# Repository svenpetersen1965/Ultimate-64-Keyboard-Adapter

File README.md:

# Ultimate-64-Keyboard-Adapter
This is an extension for the Ultimate 64 (elite) keyboard connector to get it into a position, that can be reached easily with the standard length keyboard cable. 

The project includes a 3D printed 16mm stand off, that fits the mounting hole. It fits with this 3D printed <a href="https://www.thingiverse.com/thing:3220123">mounting bracket</a> that can be found on thingiverse.com.

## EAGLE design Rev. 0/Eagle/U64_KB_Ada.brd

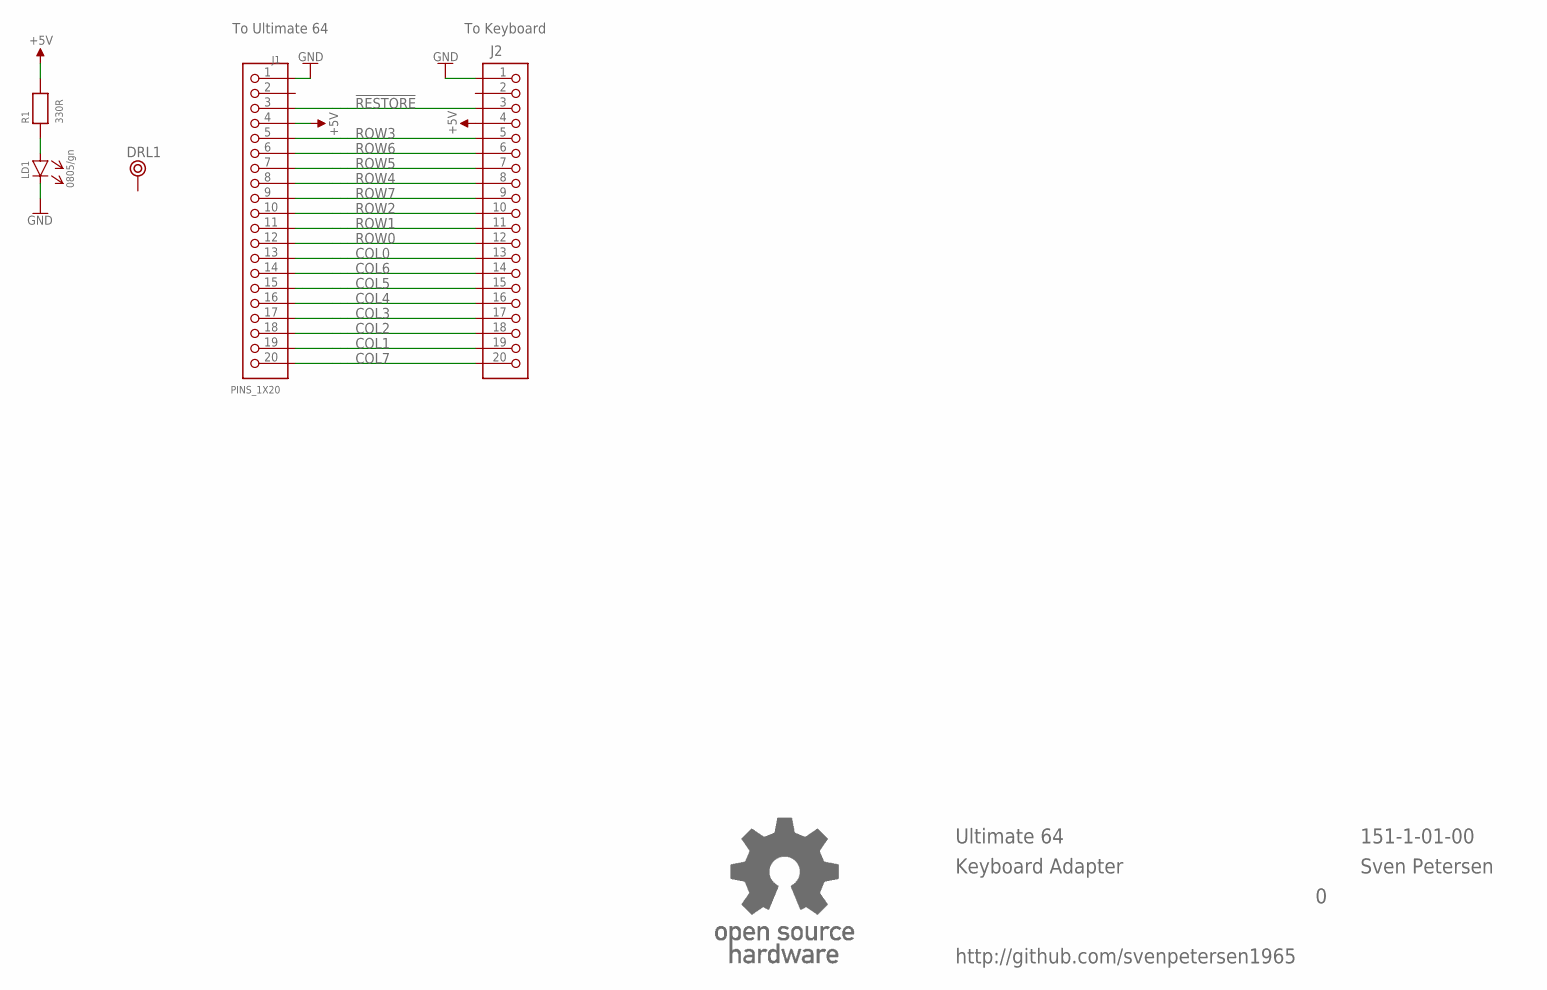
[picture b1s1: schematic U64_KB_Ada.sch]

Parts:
DRL1: BOHR3,5
J1: PINS_1X20; PINS_1X20V
J2: PINHD-1X20; 1X20
LD1: 0805/gn; 0805
R1: 330R; 0805
U$12: OPEN_SOURCE_HW; OPENHW

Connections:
!RESTORE: J1.3, J2.3
+5V: J1.4, J2.4, R1.2
COL0: J1.13, J2.13
COL1: J1.19, J2.19
COL2: J1.18, J2.18
COL3: J1.17, J2.17
COL4: J1.16, J2.16
COL5: J1.15, J2.15
COL6: J1.14, J2.14
COL7: J1.20, J2.20
GND: J1.1, J2.1, LD1.K
unnamed: LD1.A, R1.1
ROW0: J1.12, J2.12
ROW1: J1.11, J2.11
ROW2: J1.10, J2.10
ROW3: J1.5, J2.5
ROW4: J1.8, J2.8
ROW5: J1.7, J2.7
ROW6: J1.6, J2.6
ROW7: J1.9, J2.9

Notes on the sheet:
To Keyboard
To Ultimate 64
Ultimate 64
Keyboard Adapter
151-1-01-00
Sven Petersen
http://github.com/svenpetersen1965

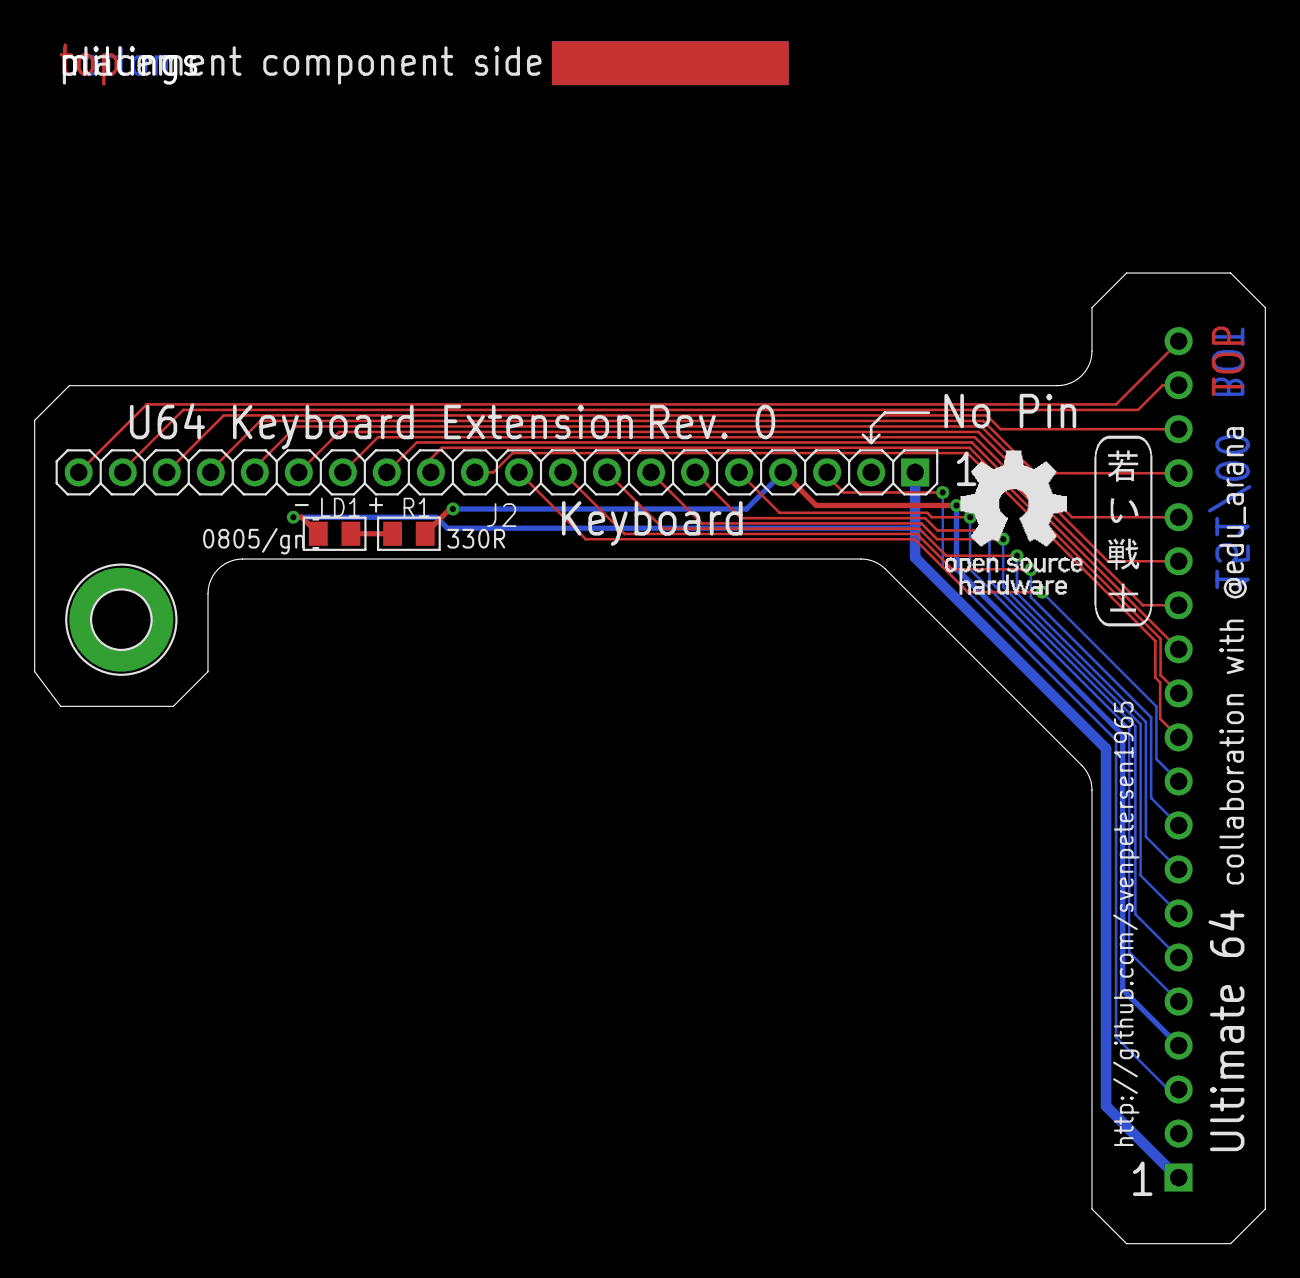
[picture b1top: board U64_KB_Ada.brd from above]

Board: 2 copper layers, 71.0 x 56.0 mm, 9 parts (1 on the bottom side), 20 nets.

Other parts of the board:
U$6: 2LAYER
U$9: SVEN_TAG
U$10: PCB-TITLE/

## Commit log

2020-08-11 Silk Screen Update
